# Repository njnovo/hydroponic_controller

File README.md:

Files I use to track the development of the hydroponic pH balance controller.

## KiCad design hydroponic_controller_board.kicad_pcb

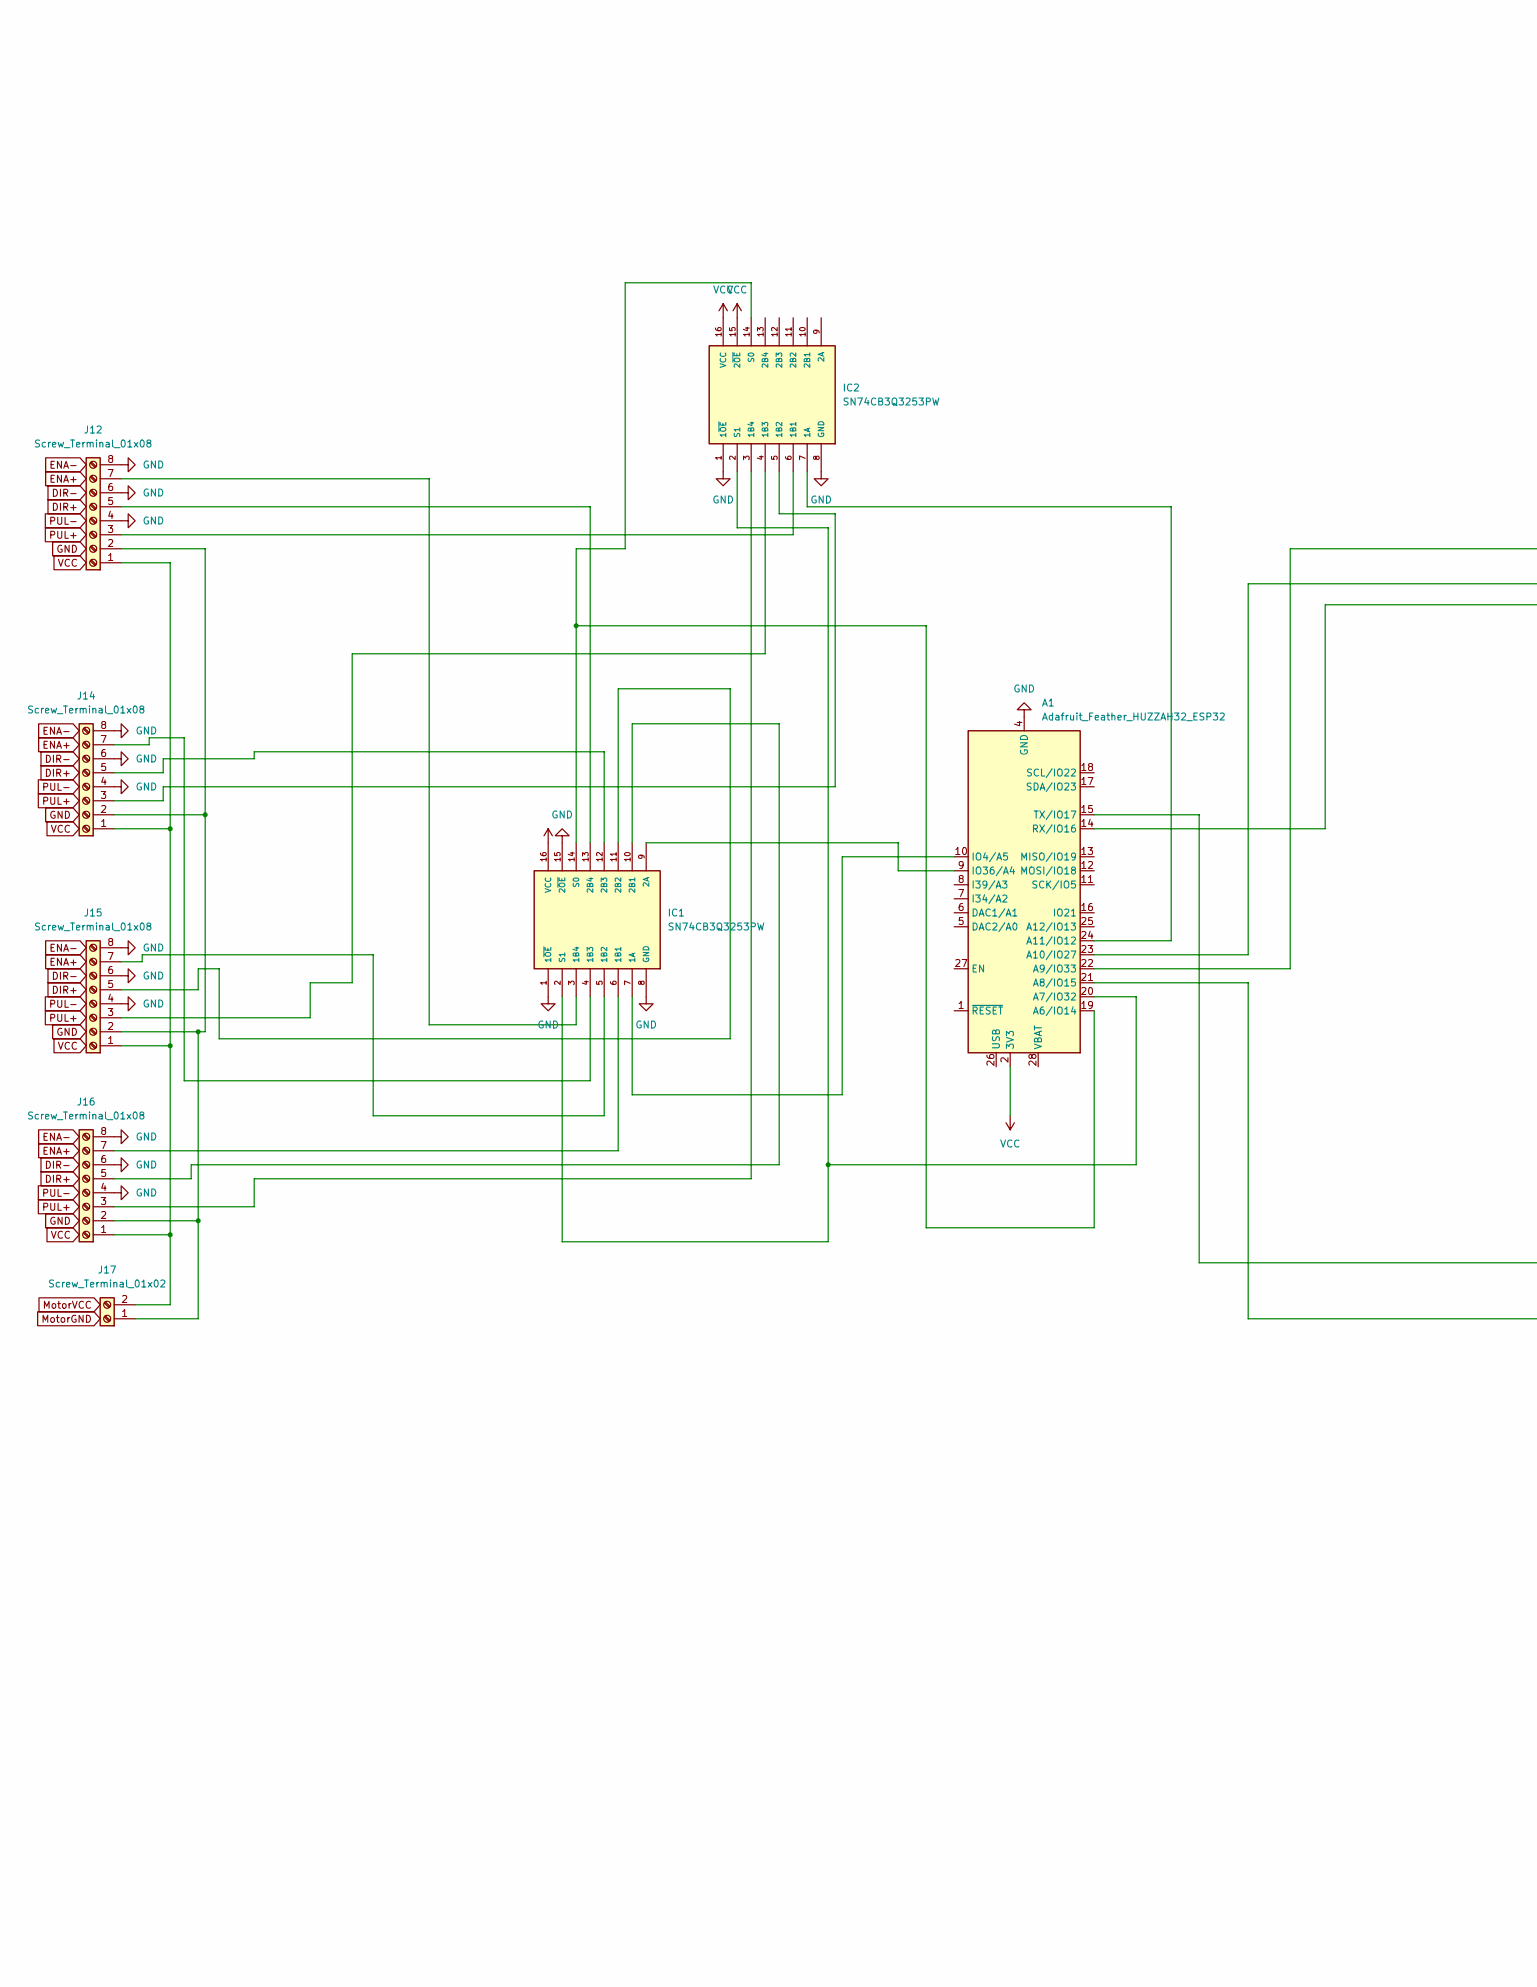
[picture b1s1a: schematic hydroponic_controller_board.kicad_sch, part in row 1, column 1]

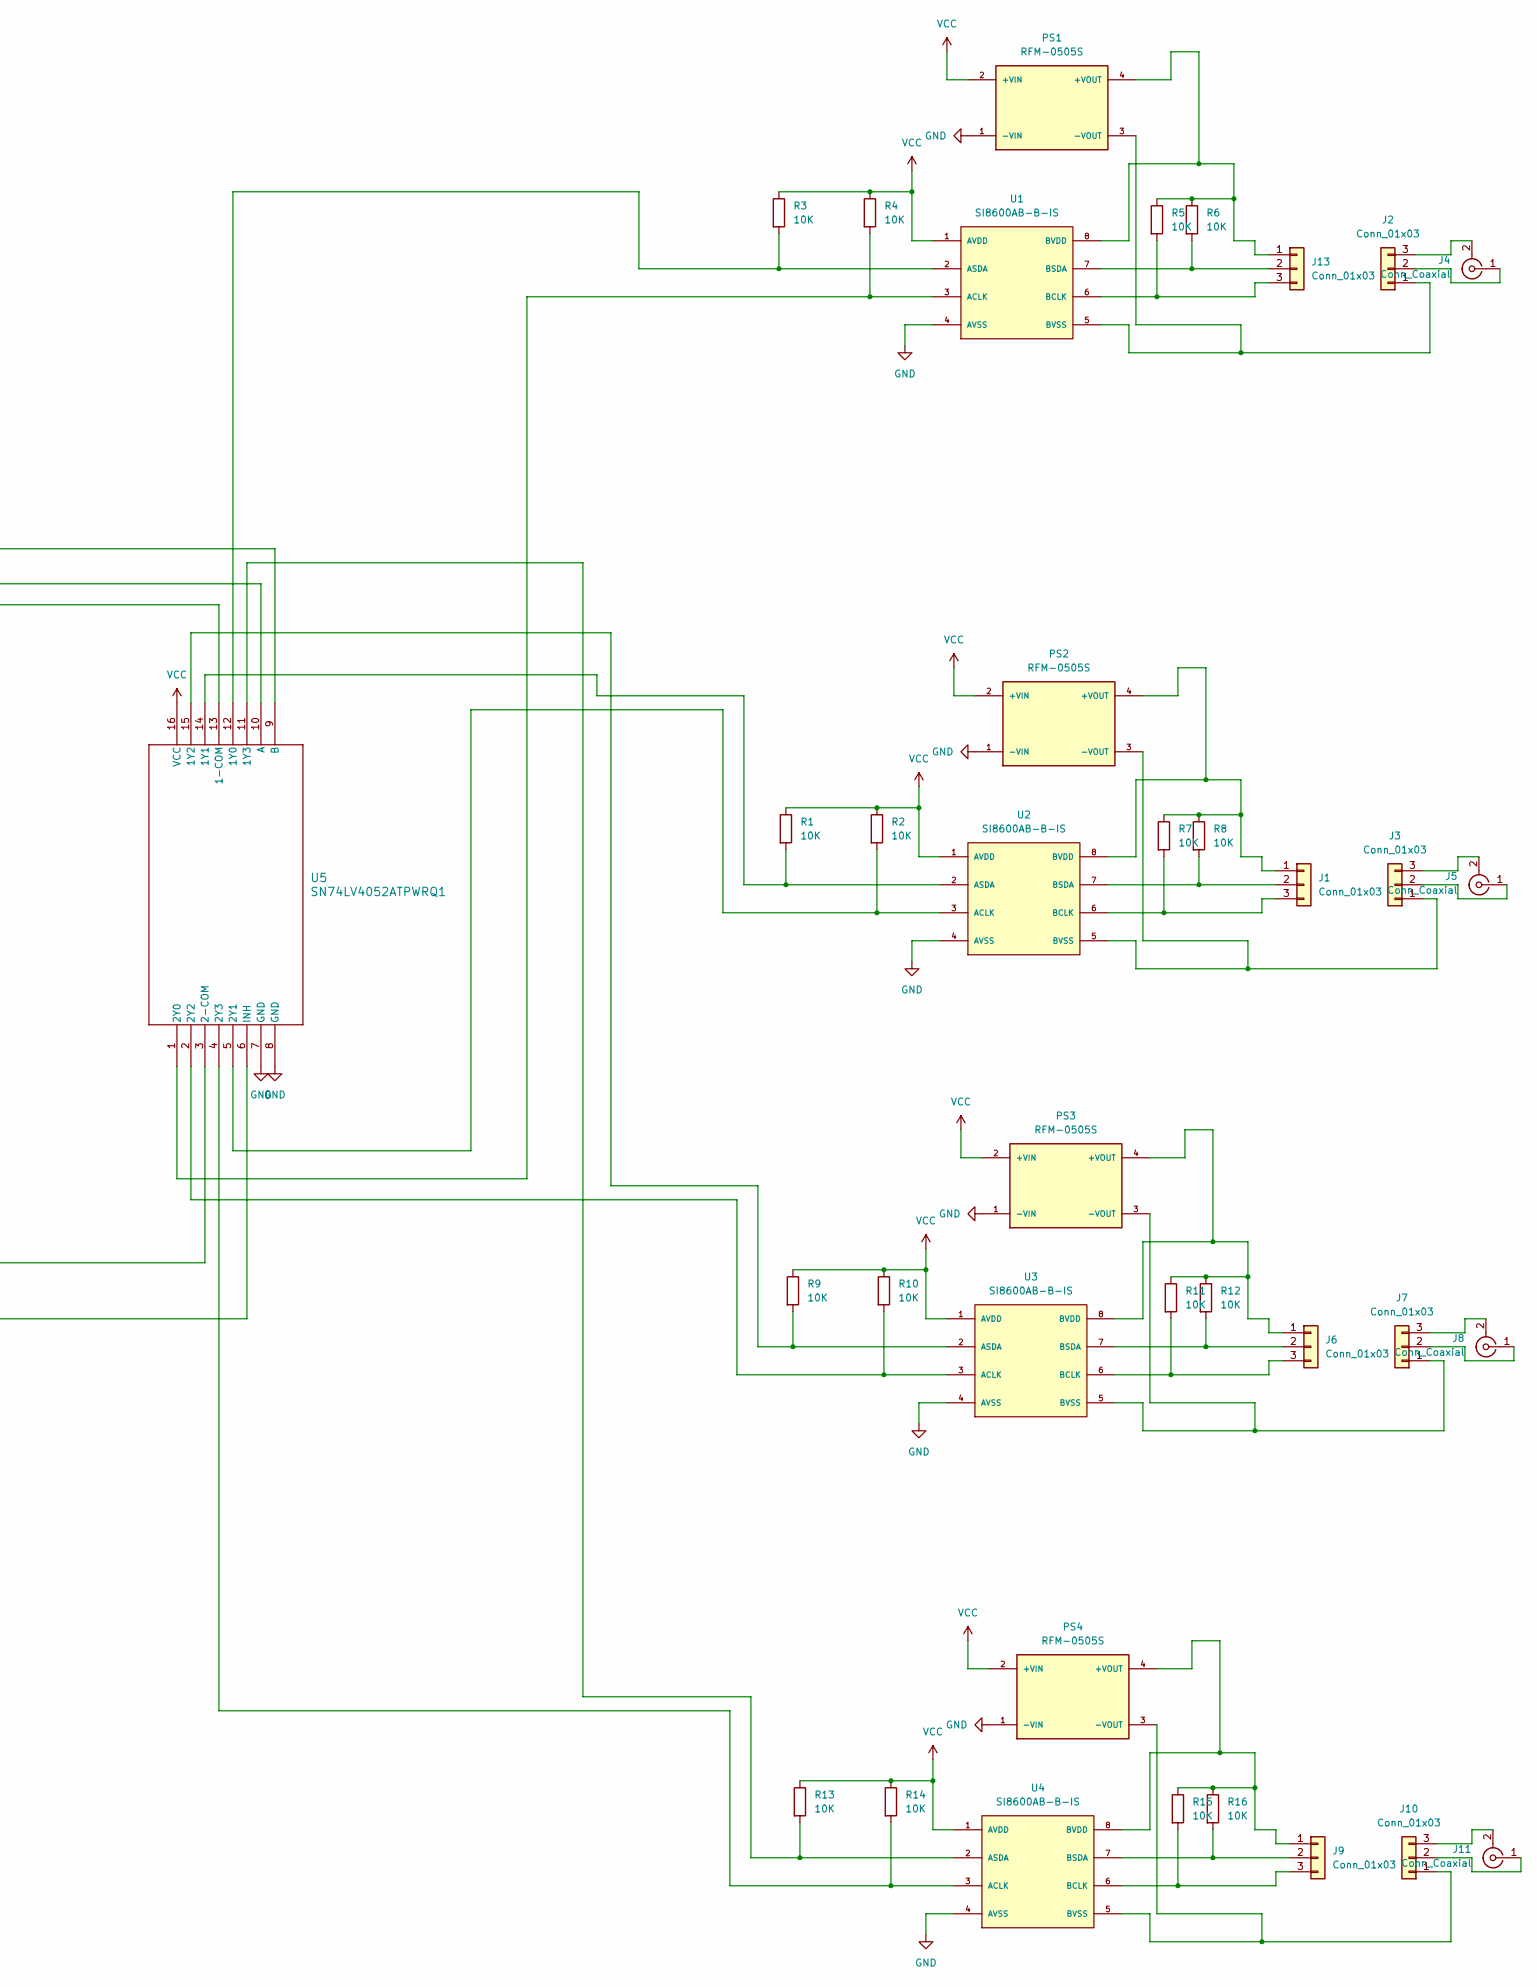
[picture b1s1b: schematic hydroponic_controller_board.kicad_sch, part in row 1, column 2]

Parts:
A1: Adafruit_Feather_HUZZAH32_ESP32; Adafruit_Feather
IC1, IC2: SN74CB3Q3253PW; PW16; MOUSER_PART_NUMBER 595-SN74CB3Q3253PW; DigiKey_Part_Number 296-26441-5-ND
J1, J2, J3, J6, J7, J9, J10, J13: Conn_01x03; PinHeader_1x03_P1.27mm_Vertical
J4, J5, J8, J11: Conn_Coaxial; SMA_Amphenol_901-143_Horizontal
J12, J14, J15, J16: Screw_Terminal_01x08; TerminalBlock_MaiXu_MX126-5.0-08P_1x08_P5.00mm
J17: Screw_Terminal_01x02; TerminalBlock_MaiXu_MX126-5.0-02P_1x02_P5.00mm
PS1, PS2, PS3, PS4: RFM-0505S; CONV_RFM-0505S; PARTREV 0
R1, R2, R3, R4, R5, R6, R7, R8, R9, R10, R11, R12, R13, R14, R15, R16: 10K; R_0805_2012Metric
U1, U2, U3, U4: SI8600AB-B-IS; SOIC127P600X175-8N
U5: SN74LV4052ATPWRQ1; PW16

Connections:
GND: A1.4 (GND), IC1.1 (1~OE), IC1.8 (GND), IC1.15 (2~OE), IC2.1 (1~OE), IC2.8 (GND), J12.4, J12.6, J12.8, J14.4, J14.6, J14.8, J15.4, J15.6, J15.8, J16.4, J16.6, J16.8, PS1.1 (-VIN), PS2.1 (-VIN), PS3.1 (-VIN), PS4.1 (-VIN), U1.4 (AVSS), U2.4 (AVSS), U3.4 (AVSS), U4.4 (AVSS), U5.7 (GND), U5.8 (GND)
unnamed: A1.19 (A6/IO14), IC1.14 (S0), IC2.14 (S0)
unnamed: A1.20 (A7/IO32), IC1.2 (S1), IC2.2 (S1)
unnamed: A1.21 (A8/IO15), U5.6 (INH)
unnamed: A1.22 (A9/IO33), U5.9 (B)
unnamed: A1.23 (A10/IO27), U5.10 (A)
unnamed: A1.24 (A11/IO12), IC2.7 (1A)
unnamed: A1.10 (IO4/A5), IC1.7 (1A)
unnamed: A1.9 (IO36/A4), IC1.9 (2A)
unnamed: A1.14 (RX/IO16), U5.13 (1-COM)
unnamed: A1.15 (TX/IO17), U5.3 (2-COM)
unnamed: IC1.6 (1B1), J16.7
unnamed: IC1.5 (1B2), J15.7
unnamed: IC1.4 (1B3), J14.7
unnamed: IC1.3 (1B4), J12.7
unnamed: IC1.10 (2B1), J16.5
unnamed: IC1.11 (2B2), J15.5
unnamed: IC1.12 (2B3), J14.5
unnamed: IC1.13 (2B4), J12.5
unnamed: IC2.6 (1B1), J12.3
unnamed: IC2.5 (1B2), J14.3
unnamed: IC2.4 (1B3), J15.3
unnamed: IC2.3 (1B4), J16.3
unnamed: J1.1, PS2.4 (+VOUT), R7.1, R8.1, U2.8 (BVDD)
unnamed: J1.2, R8.2, U2.7 (BSDA)
unnamed: J1.3, R7.2, U2.6 (BCLK)
unnamed: J2.1, PS1.3 (-VOUT), U1.5 (BVSS)
unnamed: J2.2, J4.1 (In)
unnamed: J2.3, J4.2 (Ext)
unnamed: J3.1, PS2.3 (-VOUT), U2.5 (BVSS)
unnamed: J3.2, J5.1 (In)
unnamed: J3.3, J5.2 (Ext)
unnamed: J6.1, PS3.4 (+VOUT), R11.1, R12.1, U3.8 (BVDD)
unnamed: J6.2, R12.2, U3.7 (BSDA)
unnamed: J6.3, R11.2, U3.6 (BCLK)
unnamed: J7.1, PS3.3 (-VOUT), U3.5 (BVSS)
unnamed: J7.2, J8.1 (In)
unnamed: J7.3, J8.2 (Ext)
unnamed: J9.1, PS4.4 (+VOUT), R15.1, R16.1, U4.8 (BVDD)
unnamed: J9.2, R16.2, U4.7 (BSDA)
unnamed: J9.3, R15.2, U4.6 (BCLK)
unnamed: J10.1, PS4.3 (-VOUT), U4.5 (BVSS)
unnamed: J10.2, J11.1 (In)
unnamed: J10.3, J11.2 (Ext)
unnamed: J12.1, J14.1, J15.1, J16.1, J17.2
unnamed: J12.2, J14.2, J15.2, J16.2, J17.1
unnamed: J13.1, PS1.4 (+VOUT), R5.1, R6.1, U1.8 (BVDD)
unnamed: J13.2, R6.2, U1.7 (BSDA)
unnamed: J13.3, R5.2, U1.6 (BCLK)
unnamed: R4.2, U1.3 (ACLK), U5.1 (2Y0)
unnamed: R3.2, U1.2 (ASDA), U5.12 (1Y0)
unnamed: R2.2, U2.3 (ACLK), U5.5 (2Y1)
unnamed: R1.2, U2.2 (ASDA), U5.14 (1Y1)
unnamed: R10.2, U3.3 (ACLK), U5.2 (2Y2)
unnamed: R9.2, U3.2 (ASDA), U5.15 (1Y2)
unnamed: R14.2, U4.3 (ACLK), U5.4 (2Y3)
unnamed: R13.2, U4.2 (ASDA), U5.11 (1Y3)
VCC: A1.2 (3V3), IC1.16 (VCC), IC2.15 (2~OE), IC2.16 (VCC), PS1.2 (+VIN), PS2.2 (+VIN), PS3.2 (+VIN), PS4.2 (+VIN), R1.1, R2.1, R3.1, R4.1, R9.1, R10.1, R13.1, R14.1, U1.1 (AVDD), U2.1 (AVDD), U3.1 (AVDD), U4.1 (AVDD), U5.16 (VCC)

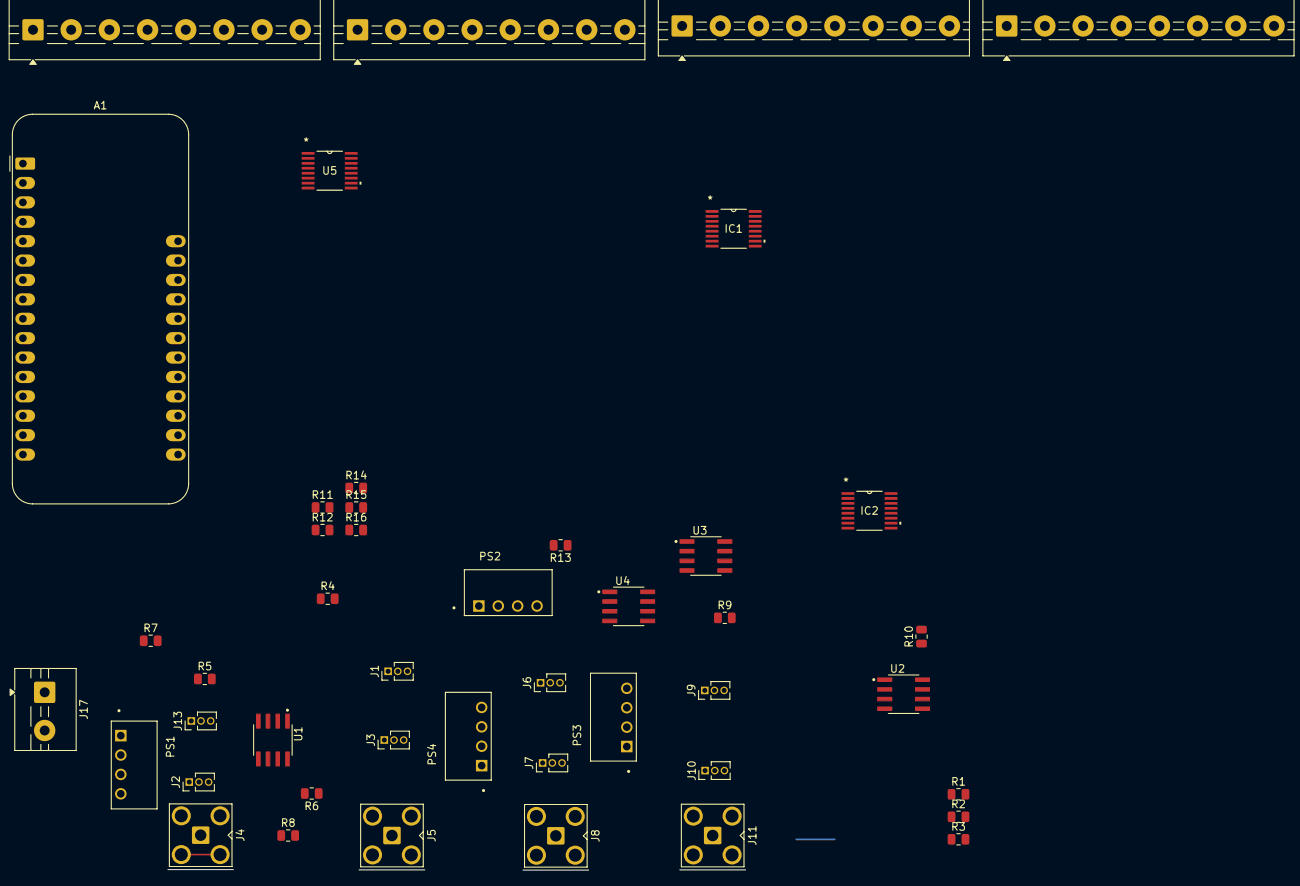
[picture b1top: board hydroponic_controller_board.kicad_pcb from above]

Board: 2 copper layers, 45 parts (0 on the bottom side), 58 nets.

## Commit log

2025-08-05 Initial checkin
